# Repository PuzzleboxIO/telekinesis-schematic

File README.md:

EEG design based on the 8-bit OpenBCI with a TI ADS1299 and an Intel Curie Module

For more information please visit:

http://puzzlebox.io/telekinesis

Contributors:

Tomás Vega [https://github.com/tomasero]

Kelly Peng [https://github.com/GameCracker]

Design software format:

EAGLE PCB

Screenshots:

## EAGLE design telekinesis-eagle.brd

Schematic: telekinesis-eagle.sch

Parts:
BATT: JST_2PIN; JSTPH2
C1, C25, C31, C33, C40: 10 uF; C0805K
C2: 100 uF; C/6032-28R
C3, C9, C11, C28, C35: CKCL44X7R1H102M0B5AA; CKCL44
C5, C6, C7, C14, C17, C18, C19, C21, C22, C29: 1 uF; C0805K
C12, C13, C15, C24, C26, C27, C30, C46: 0.1 uF; C0805K
C16: 1 nF; C0805K
C20, C23: 9 pF; C0805K
C32: 0.01 uF; C0805K
C34, C36, C37, C39, C41, C43, C44, C45: 2.2 uF; C0805K
C38: 0.01uF; C0805K
C42: 100 uF; C0805K
D2, D3, D4, D5, D6, D7: QUAD_TVS
D8: BLUE; SML0603
D9: DIODESOD-123; SOD-123
IC1: MEGA8-AI; TQFP32-08
IC2: IC_BUFF_SN74LVC8T245; SOIC-24
PROGRAM: DPDT; AYZ0202
R1, R2, R3, R4, R6: 2.2k; CAY16
R5: 1M; R0805W
R8: 10K; R0805W
R9: 470K; R0805W
R12: 1K; R0805W
S1: SWITCH-MOMENTARY-2SMD-REDUNDANT; TACTILE-SWITCH-SMD
SV1: MA13-2W
SW1: SWITCH_SPST; SPST_SMT_19192
U3: LM2664; SOT-23-6
U4: TLV700XX; SC70-5
U5, U9: LP5907
U6: ADS_1299; TQFP64_ADS
U$5: ORB_0; ORB_52_22MM
UART: M03PTH; 1X03
UARTCONNECT: DPDT; AYZ0202
VR1: TPS72325; SM
X1: CSM-7X-DU

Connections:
1N: D3.4 (IO3), R1.1, SV1.21
1P: D2.1 (IO1), R1.2 (1), SV1.22
2N: D3.2 (IO2), R2.3 (1), SV1.19
2P: D3.5 (IO4), R2.4 (1), SV1.20
3N: D4.4 (IO3), R2.1, SV1.17
3P: D3.1 (IO1), R2.2 (1), SV1.18
4N: D4.2 (IO2), R3.3 (1), SV1.15
4P: D4.5 (IO4), R3.4 (1), SV1.16
5N: D5.4 (IO3), R3.1, SV1.13
5P: D4.1 (IO1), R3.2 (1), SV1.14
6N: D5.2 (IO2), R4.3 (1), SV1.11
6P: D5.5 (IO4), R4.4 (1), SV1.12
7N: D6.4 (IO3), R4.1, SV1.9
7P: D5.1 (IO1), R4.2 (1), SV1.10
8N: D6.2 (IO2), R6.3 (1), SV1.7
8P: D6.5 (IO4), R6.4 (1), SV1.8
+5V: C26.1, C39.2, C41.2, C42.2, C44.2, IC1.4 (VCC), IC1.6 (VCC), IC1.18 (AVCC), IC2.24 (VCCB1), R8.2, R9.2, U3.4 (SD), U3.5 (V+), U4.1 (IN), U4.3 (EN), U5.1 (VIN), U5.3 (EN), U9.5 (OUT), U$5.26 (36)
+UB: C13.1, C17.1, C22.1, C24.1, C29.1, C30.1, C36.2, C40.1, D7.2 (IO2), SV1.1, SV1.2, U4.5 (OUT), U6.19 (AVDD3), U6.21 (AVDD4), U6.22 (AVDD), U6.35 (/PWDN), U6.54 (AVDD_1), U6.56 (AVDD2), U6.59 (AVDD1)
-RAW: C33.1, C37.2, U3.2 (OUT), VR1.2 (IN), VR1.3 (EN)
-UB: C1.1, C2.-, C5.1, C6.2, C7.2, C13.2, C15.1, C17.2, C18.1, C19.1, C21.1, C31.1, C34.2, D2.4 (IO3), SV1.25, SV1.26, U6.20 (AVSS2), U6.23 (AVSS1), U6.25 (VREFN), U6.32 (AVSS), U6.53 (AVSS_1), U6.57 (AVSS3), U6.58 (AVSS4), VR1.5 (OUT)
A0: IC1.23 (PC0(ADC0))
A1: IC1.24 (PC1(ADC1))
A2: IC1.25 (PC2(ADC2))
A3: IC1.26 (PC3(ADC3))
A6: IC1.19 (ADC6)
A7: IC1.22 (ADC7)
ARDUINO_RESET: C46.2, IC1.29 (PC6(/RESET)), R8.1, S1.3 (2), S1.4 (2)
AREF: C27.1, IC1.20 (AREF)
BIAS: D7.4 (IO3), R6.1, SV1.5, SV1.6
BIAS_DRV: C16.2, C35.8, R5.2, R6.8 (2)
BIAS_INV: U6.61 (BIAS_INV)
BOOT_EN: C46.1
CLK: U6.37 (CLK)
CS1: IC2.8 (A6), U6.39 (/CS)
CS2: IC2.6 (A4)
CS3: IC2.5 (A3)
CS4: IC2.4 (A2)
DVDD: C12.1, C14.1, C43.2, IC2.1 (VCCA), U5.5 (OUT), U6.48 (DVDD2), U6.50 (DVDD1), U6.52 (CLKSEL)
GND: C3.1, C3.2, C3.3, C3.4, C9.1, C9.2, C9.3, C9.4, C11.1, C11.2, C11.3, C11.4, C12.2, C14.2, C18.2, C21.2, C22.2, C24.2, C28.1, C28.2, C28.3, C28.4, C29.2, C30.2, C31.2, C32.1, C33.2, C34.1, C35.1, C35.2, C35.3, C35.4, C36.1, C37.1, C38.1, C39.1, C40.2, C41.1, C42.1, C43.1, C44.1, C45.1, D2.3 (GND), D3.3 (GND), D4.3 (GND), D5.3 (GND), D6.3 (GND), D7.1 (IO1), D7.3 (GND), D9.A, IC2.2 (DIR), IC2.11 (GND1), IC2.12 (GND2), IC2.13 (GND3), IC2.22 (OE), R6.2 (1), R6.7 (2), R12.1, SV1.3, SV1.4, U3.1 (GND), U4.2 (GND), U5.2 (GND), U6.31 (RESV1), U6.33 (DGND), U6.41 (DAISY_IN), U6.49 (DGND1), U6.51 (DGND2), U6.60 (BIAS_REF), U6.64 (RESERVED), U9.2 (GND), U$5.1 (47), UART.3, VR1.1 (GND)
IN1N: C3.8, R1.8 (2), U6.15 (IN1N)
IN1P: C3.7, R1.7 (2), U6.16 (IN1P)
IN2N: C9.6, R2.6 (2), U6.13 (IN2N)
IN2P: C9.5, R2.5 (2), U6.14 (IN2P)
IN3N: C9.8, R2.8 (2), U6.11 (IN3N)
IN3P: C9.7, R2.7 (2), U6.12 (IN3P)
IN4N: C11.6, R3.6 (2), U6.9 (IN4N)
IN4P: C11.5, R3.5 (2), U6.10 (IN4P)
IN5N: C11.8, R3.8 (2), U6.7 (IN5N)
IN5P: C11.7, R3.7 (2), U6.8 (IN5P)
IN6N: C28.6, R4.6 (2), U6.5 (IN6N)
IN6P: C28.5, R4.5 (2), U6.6 (IN6P)
IN7N: C28.8, R4.8 (2), U6.3 (IN7N)
IN7P: C28.7, R4.7 (2), U6.4 (IN7P)
IN8N: C35.6, R6.6 (2), U6.1 (IN8N)
IN8P: C35.5, R6.5 (2), U6.2 (IN8P)
MOSI: IC2.9 (A7), U6.34 (D_IN)
unnamed: IC1.32 (PD2(INT0)), R9.1
unnamed: C20.2, IC1.7 (PB6(XTAL1/TOSC1)), X1.2
unnamed: C23.2, IC1.8 (PB7(XTAL2/TOSC2)), X1.1
unnamed: C16.1, R5.1, U6.62 (BIAS_IN), U6.63 (BIAS_OUT)
unnamed: C15.2, C19.2, U6.55 (VCAP3)
unnamed: C6.1, U6.26 (VCAP4)
unnamed: C1.2, C5.2, U6.24 (VREFP)
unnamed: C2.+, U6.28 (VCAP1)
unnamed: C25.1, U3.6 (CAP+)
unnamed: C7.1, U6.30 (VCAP2)
unnamed: C25.2, U3.3 (CAP-)
unnamed: C32.2, VR1.4 (NR)
unnamed: D8.C, R12.2
unnamed: C38.2, U9.4 (NC)
NC: IC2.23 (VCCB2), U6.27 (NC1), U6.29 (NC)
NULL: BATT.1, D9.C
PE: C20.1, C23.1, C26.2, C27.2, IC1.3 (GND), IC1.5 (GND), IC1.21 (GND), S1.1, S1.2 (1)
RAW: BATT.2, SW1.B
RAW_SWITCH: C45.2, SW1.C (S), U9.1 (VIN), U9.3 (EN)
RESET: IC2.7 (A5), U6.36 (/RESET)
RX: PROGRAM.2, UART.2
RX_ATM: IC1.30 (PD0(RXD)), PROGRAM.4, UARTCONNECT.5
RX_ORB: PROGRAM.6, U$5.33 (17), UARTCONNECT.1
SCL: IC1.28 (PC5(ADC5/SCL)), U$5.10 (9)
SCLK: D8.A, IC2.10 (A8), U6.40 (SCLK)
SDA: IC1.27 (PC4(ADC4/SDA)), U$5.9 (8)
SRB1: D2.5 (IO4), R1.4 (1), SV1.24
SRB2: D2.2 (IO2), R1.3 (1), SV1.23
TX: PROGRAM.5, UART.1
TXD: IC2.3 (A1)
TX_ATM: IC1.31 (PD1(TXD)), IC2.21 (B1), PROGRAM.1, UARTCONNECT.2
TX_ORB: PROGRAM.3, U$5.31 (19), UARTCONNECT.4
_CS1: IC1.14 (PB2(SS/OC1B)), IC2.16 (B6)
_CS2: IC1.11 (PD7(AIN1)), IC2.18 (B4)
_CS3: IC1.10 (PD6(AIN0)), IC2.19 (B3)
_CS4: IC1.9 (PD5(T1)), IC2.20 (B2)
_DRDY: IC1.12 (PB0(ICP)), U6.47 (/DRDY)
_INT1: IC1.1 (PD3(INT1))
_MISO: IC1.16 (PB4(MISO)), U6.43 (DOUT)
_MOSI: IC1.15 (PB3(MOSI/OC2)), IC2.15 (B7)
_RESET: IC1.13 (PB1(OC1A)), IC2.17 (B5)
_SCLK: IC1.17 (PB5(SCK)), IC2.14 (B8)
_SRB1: C3.5, R1.5 (2), U6.17 (SRB1)
_SRB2: C3.6, R1.6 (2), U6.18 (SRB2)

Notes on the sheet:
5V Regulator
2.5V Regulator
-2.5V Regulator
Input Connector
ADS1299
ATmega328
5V Inverter
ADS Decoupling
Blue Led
Filtro
3V Regulator
Intel Curie

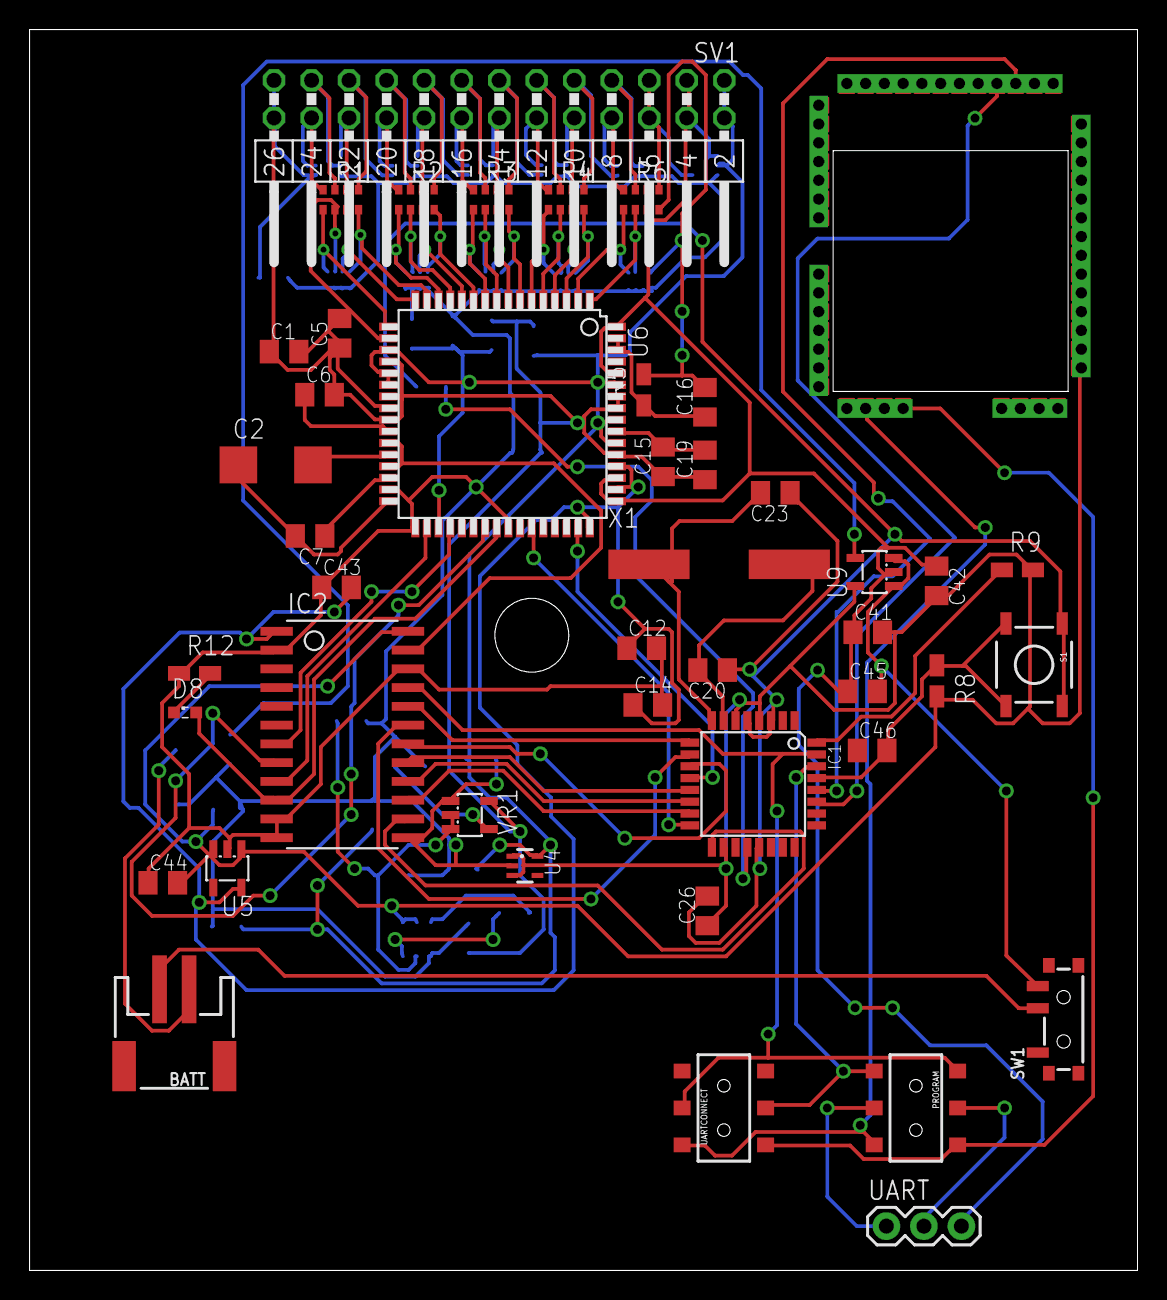
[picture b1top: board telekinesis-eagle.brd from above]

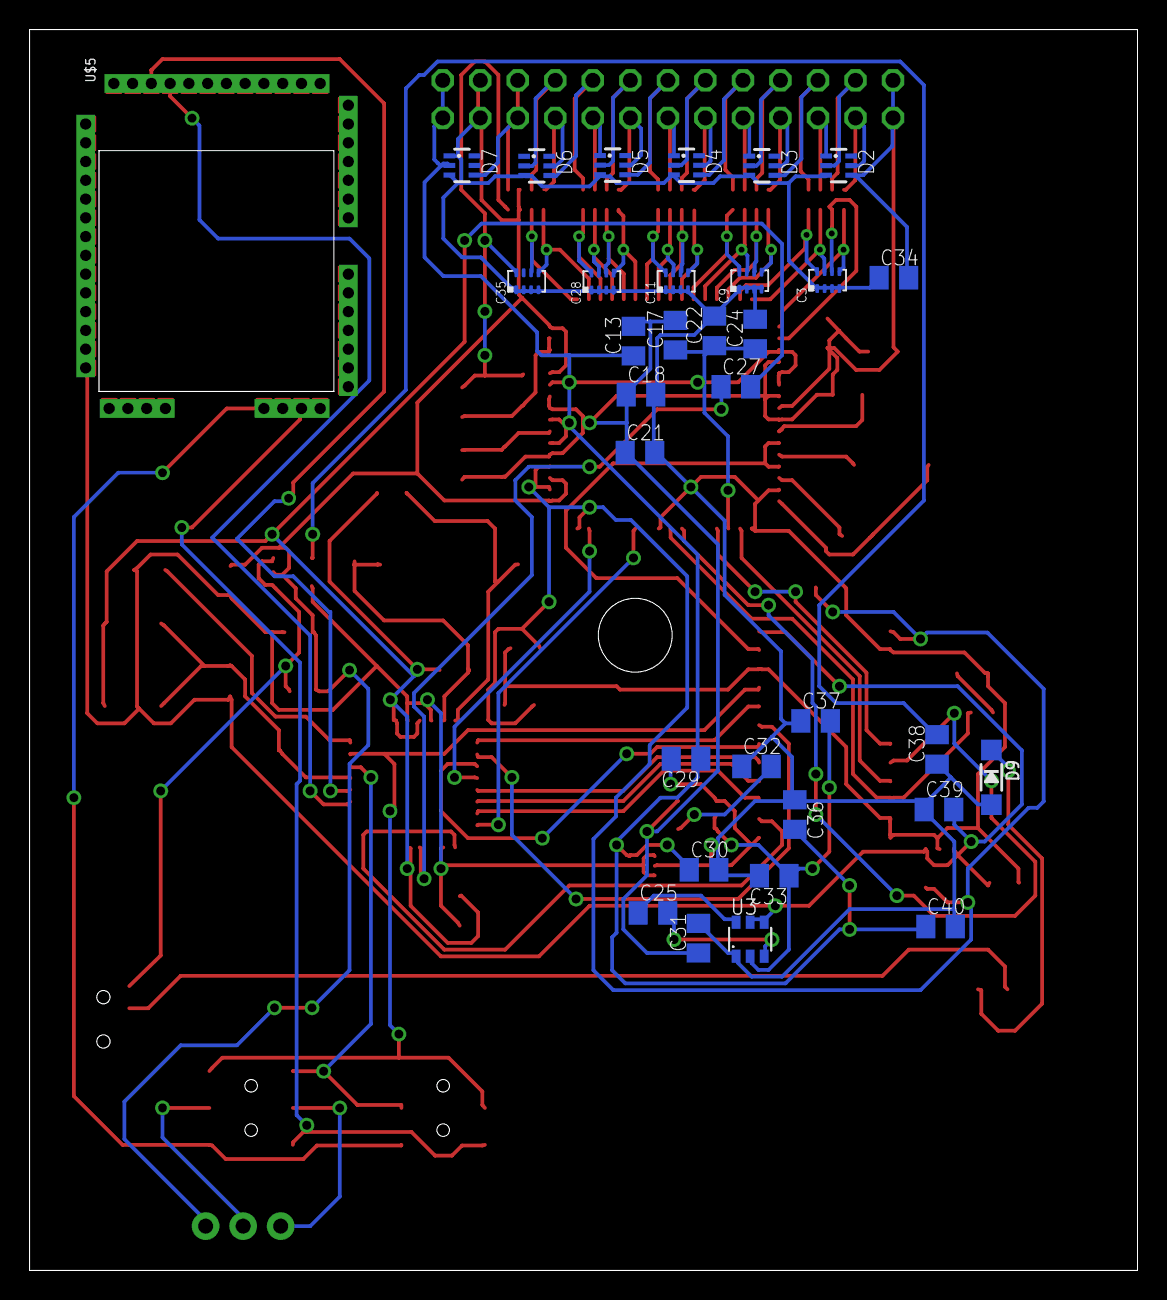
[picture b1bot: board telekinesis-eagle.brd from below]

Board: 2 copper layers, 75.0 x 84.0 mm, 77 parts (33 on the bottom side), 86 nets.

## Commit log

2016-04-13 - initial commit
2016-04-13 - correction for source version from OpenBCI (32-bit to 8-bit)
2016-04-14 - removed backup files
2016-04-15 - contributor credits added
2016-04-19 - screenshots added

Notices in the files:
parts and their libraries:
microbuilder: This work is placed in the public domain, and may be freely used for commercial and non-commercial work with the following conditions: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
SparkFun-Electromechanical: Licensing: Creative Commons ShareAlike 4.0 International - https://creativecommons.org/licenses/by-sa/4.0
